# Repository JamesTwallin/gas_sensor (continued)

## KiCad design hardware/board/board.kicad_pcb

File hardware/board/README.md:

# Phone-companion board

A 66 × 36 mm, 4-layer board: bare ESP32-S3-MINI-1, two bare Figaro TGS sensors,
two ADS1115s, an SHT40, LiPo charging and a 5 V heater boost, plus a socket for
the [air blade](../air_blade/) (airflow thermistor and outside-air SHT40) and pads
for a CO module and a fan. The phone does the rest: position, display, storage
and the app. The electrical and Bluetooth spec is
[docs/phone_board.md](../../docs/phone_board.md). What the board measures and
why, with plots: [docs/board.md](../../docs/board.md).

Next to the first phone-companion board, with what is new boxed:

**Status: made and working.** JLCPCB made and assembled the boards, and they
passed a bench test on 2026-10-22. Three things to know when you first power one:

- **The boards arrive with blank flash.** Nothing runs until you flash the
  firmware.
- **The power switch (SW1) must be ON, even on USB.** It gates the 3.3 V
  regulator, so with it off the ESP32 has no power and the USB port does not
  appear.
- **The first flash needs the BOOT and RESET buttons.** Hold BOOT, press and
  release RESET, then let go of BOOT, and do a full upload (see
  [Firmware](#firmware)).

The board **fits the printed case** ([hardware/enclosure](../enclosure/),
`case.scad`): the mounting holes, sensor cans, USB-C, power switch, LED, BOOT
button and the SHT40 tongue are where the first board had them. The RST button
sits right above BOOT, so use the current front shell, `stl/front.stl`: it has
RST's pen hole in the right place and a slot for the air blade between the
sensor caps. The back shell is `stl/back.stl` and the car mount
`stl/car_adapter.stl`.

The board adds what the first survey analysis ([docs/REPORT.md](../../docs/REPORT.md))
showed was missing:

- **Airflow.** Air moving over the gas sensors cools their heaters and moves
  their readings as much as a small gas plume. The first board could not
  measure it.
- **Outside air.** The on-board SHT40 reads the air *inside the case*: on every
  drive it read 0.6–0.9 °C warmer at walking pace than at motorway speed, and
  28–32 °C during an indoor stop, because the heaters warm the case and airflow
  cools it. The detector needs the temperature and humidity of the air the
  sensors are sampling. The air blade carries a second SHT40 out in the air
  beside the sensor caps.
- **Exhaust versus gas.** Exhaust contains CO; mains gas does not.

## The air blade cannot be fitted yet

**Do not order the current air blade** ([hardware/air_blade](../air_blade/)).
J3, the board's socket for it, sits in a 3.8 mm gap between the two sensor cans,
which are 13 mm tall, and its pads stop 0.3 mm short of the blade's notch. There
is no realistic way to get a soldering iron in there and join the blade to the
pads. The blade is being redesigned. Until then the board runs without it: the
firmware uses the on-board SHT40 and reports no airflow.

## Layout

The ESP32 sits at the rear with its antenna over the left edge. The two Figaro
cans are at the front edge. USB-C is on the bottom edge and the switch on the
top edge, both in the middle.

- **Front (right) end: the gas inlet.** The two cans, each with a 0.5 Ω heater
  shunt beside its heater-return pin (R22 above CH4, R25 between the cans), and
  **J3**, the air blade's socket: five pads beside a notch in the board's end,
  in the gap between the cans where the air arrives (labelled BLADE). The
  [air blade](../air_blade/) is meant to stand in the notch, soldered to J3, and
  poke out through a slot in the case face. See above for why that does not
  work with the current blade.
- **Analogue block, just inboard of the cans.** ADS1115 #1 (U6) and #2 (U8)
  side by side; the heated thermistor's feed (R28/C24) above them;
  U8's 3V3-monitor divider (R33/R34/C27) below; the gas-sensor load networks.
- **Top edge.** **J4**, six pads for the CO module and a fan (labelled
  5V G TX RX 5V G), with R30 beside it.
- **Middle.** The boost loop (hand-routed) with the VSYS bulk capacitors C28/C29
  at its input; the battery and heater-rail dividers (R13/R14, R15/R16) in one
  row next to it.
- **Rear, by the ESP32.** The filter capacitors of the battery and heater-rail
  monitors (C13, C14) right at the ESP32 pins they feed.
- **Buttons and test pads.** RST and BOOT stacked one above the other by the
  USB edge; the serial/supply test pads in one row beside them, labelled
  TX RX GND 3V3.
- **SHT40 tongue (bottom-left).** The on-board SHT40, cut free on two sides by a
  slot. It reads the case air, and is logged as the case reading when the air
  blade is fitted.

## What it adds over the first board

| | Parts | What it does |
|---|---|---|
| **J3** + edge notch | 5 pads, 1.0 mm pitch: heated thermistor, GND, 3V3, SCL, SDA | socket for the [air blade](../air_blade/): an outside-air SHT40 (0x46, or 0x45) and the heated airflow thermistor, out in the air between the sensor caps. The current blade cannot be soldered to it (see above) |
| R28 1k, C24 | | feed the blade's heated thermistor 2.7 mW (about 1 °C above the air) |
| **U6** AIN2 | | reads the heated thermistor (16-bit); AIN3 is spare |
| GPIO1 / GPIO2 | C13, C14 at the pins | read VBAT and the heater rail on the ESP32's own ADC |
| **R22, R25** | 0.5 Ω, 0603 | in each sensor's heater return, so the heater current can be measured; fit 0 Ω links to switch this off |
| **U8** | ADS1115 at 0x49, C26 | reads both heater currents and, through R33/R34/C27, the 3.3 V rail (the thermistor dividers are not ratiometric to the ADC) |
| **J4** | 6 pads, 1.27 mm pitch: +5V, GND, TX in, RX out, +5V, GND; R30 1k | a Winsen ZE15-CO / ZE07-CO module (5–12 V, so it runs from the heater rail) and an optional 5 V fan. Pin 1 doubles as the +5 V test point |
| C28, C29 | 22 µF on VSYS | more margin when the heaters start on USB power alone (the first board browned out there) |
| SW2 (RST), TP1–TP4 | | RST right above BOOT; the test pads in a row beside them |

Pin by pin, where the board differs from the first board:

| | first board | this board |
|---|---|---|
| ADS1115 #1 (0x48) AIN2 / AIN3 | VBAT / 2, +5V_HTR / 2 | heated thermistor (air blade), spare |
| I²C bus | ADS1115 0x48, SHT40 0x44 | adds ADS1115 #2 0x49 and the air blade's SHT40 0x46 (or 0x45) |
| ADS1115 #2 (0x49) | — | AIN0 CH4 heater current, AIN1 LPG heater current, AIN2 +3V3 / 2, AIN3 spare |
| ESP32 GPIO1 / GPIO2 | backup reads of the gas taps (links never fitted) | VBAT / 2, +5V_HTR / 2 |
| GPIO43 / GPIO44 | test pads | test pads, and the CO module on J4 |
| Figaro pin 4 (heater −) | GND | 0.5 Ω shunt to GND |

## Firmware

```
pio run -d firmware/phone_board -e board --target upload
```

`board` is the default build target. On a new board, put the ESP32 into its
bootloader first (hold BOOT, tap RESET, release BOOT) and do a full upload,
because the flash is blank. After that, plain uploads work.

The firmware sends the board ID `rev-e` (a fixed value in the protocol). It
reads the heated thermistor on the ADS1115, and VBAT and the heater rail on the
ESP32. When the air blade's SHT40 answers (0x45 or 0x46), it supplies the
temperature and humidity (to the phone and to the detector) and the ambient for
the airflow calculation; the on-board readings are logged as `case_temp_c` /
`case_rh_pct` on USB serial, and the Info JSON says `"t_src":2`. Without the
blade it falls back to the on-board SHT40 (`"t_src":0`). The heater currents
(`ch4_htr_ma`, `lpg_htr_ma`) and the rail (`v3v3_mv`) go to the USB serial log
only for now: they are for a bench experiment first.

**The detector's coefficients were fitted on case-air readings.** With the
air blade fitted they need refitting from new surveys before the
detector's numbers mean anything ([docs/REPORT.md](../../docs/REPORT.md),
`python tools/replay.py fit`).

## The design is generated — edit `gen/design.py`, not the KiCad files

`gen/design.py` holds every part, net, LCSC number, placement, pre-routed track
and rule, and the scripts build the KiCad project from it:

| Step | Command | Output |
|---|---|---|
| custom symbols | `python gen/build_lib.py` | `lib/phone_board.kicad_sym` |
| schematic | `python gen/build_sch.py` | `board.kicad_sch` |
| board (placed, unrouted) | `"C:\Program Files\KiCad\9.0\bin\python.exe" gen/build_pcb.py` | `board.kicad_pcb`, `.kicad_pro` |
| autoroute | `...\python.exe gen/route.py` | routed board, GND pours + stitching vias |
| tidy silkscreen labels | `...\python.exe gen/tidy_silk.py` | |
| JLC placement | `...\python.exe gen/jlc_align.py` | `gen/jlc_placement.json` |
| fab files + renders | `python gen/export.py` | `production/`, `preview/` |
| relabel silkscreen only | `...\python.exe gen/build_pcb.py --silk-only` | edits the routed board in place |

Extra helpers: `gen/courtyards.py` prints footprint courtyards for checking
placement by hand; `gen/islands.py` and `gen/anchor_fills.py` find and anchor
unconnected ground-fill islands; `gen/add_keepouts.py` adds a keepout to a
routed board without re-routing; `gen/note_plots.py` draws the plots in
docs/board.md.

The middle of the board is dense, so a number of links are hand-routed
(`PREROUTE`) rather than left to the autorouter: the SDA trunk on In2, TXD0 to
the CO pads along the top strip on In2 and down B.Cu to the TX test pad, the
heater-rail divider feed, the two monitor lines from GPIO1/GPIO2 to their
capacitors, the 3V3-divider node, the J4 +5V pair, and short ground drops for
both ADS1115s, the air blade socket, the LPG shunt and the monitor capacitors
(where the ground fill cannot reach).

The air blade socket (J3) uses a project footprint,
`lib/phone_board.pretty/BladeSocket_1x05_P1.0mm`, and the notch is `NOTCHES` in
`gen/design.py`.

`route.py` needs the `JAVA` and `FREEROUTING` environment variables set to the
Java 25 runtime and the Freerouting 2.4.1 jar.

Checks: `kicad-cli pcb drc --schematic-parity board.kicad_pcb` and
`kicad-cli sch erc board.kicad_sch`.

Last run (2026-10-10, after adding the air blade socket and notch):
`kicad-cli pcb drc --schematic-parity` reports **0 violations, 0 unconnected
items, 0 schematic/board mismatches**; `kicad-cli sch erc` reports **0 errors,
0 warnings**; `gen/jlc_align.py` has corrected the CPL against LCSC's
footprints. Freerouting doesn't route the same way twice: after a rebuild, re-run
the checks.

## Ordering from JLCPCB

1. **PCB:** upload `production/gerbers.zip`. 4 layers, 1.6 mm. Minimums:
   0.2 mm track/clearance (0.15 mm at the SOT-563), 0.3 mm vias, and 0.2 mm drill
   for the via-in-pad GND vias under the ESP32, the charger and the two
   ADS1115s.
2. **Assembly:** top side, `production/bom.csv` and `production/cpl.csv` (already
   corrected for JLC's library by `gen/jlc_align.py`; still look over the preview,
   especially the pin-1 dots). Parts that are easy to miss in the BOM: the 0.5 Ω
   0603 shunts (FRL0603FR500TS, C2934253) and the second ADS1115 (C37593).
   **Do not order the current [air blade](../air_blade/)** with it: it cannot
   be soldered to J3 (see [above](#the-air-blade-cannot-be-fitted-yet)).
3. **Solder yourself:**
   - **Figaro TGS2611-E00 (S1, CH4) and TGS2610-D00 (S2, LPG)**, from RS
     Components (134-6647 and 134-6641). Burn them in for 4–7 days.
   - If used, **the CO module and fan on J4**
     ([docs/HARDWARE.md](../../docs/HARDWARE.md) section 2). The pads are 1.27 mm
     apart: solder thin wire straight on.

## Before you power it

Check the battery polarity (J2 pin 1 = −, pin 2 = +), and on first bring-up check
+3V3 on TP4 before fitting the sensors (SW1 must be ON). +5V_HTR is on J4 pin 1;
it stays at 0 V until the firmware drives GPIO7 high.

- **When an air blade is fitted, its tip must stand in free air,** 4.5 mm out of
  the slot, touching nothing: the heated thermistor reads airflow by how fast it
  loses heat.

## Known limitations

- The battery charger draws a little from the cell even when the board is off,
  the charge current is fixed at 500 mA, and the schematic is joined up by net
  labels rather than drawn wires.
- **The air blade cannot be fitted yet** (see above), so the airflow and
  outside-air readings are untested on this board.
- Still to be measured:
  - whether the heater current changes measurably with airflow (Figaro does not
    publish the heater's temperature coefficient);
  - the VBAT reading through the 1M/1M divider on the ESP32's ADC (C13 holds the
    charge; calibrate against a meter);
  - how much the blade's thermistor self-heats and how strongly it follows
    airflow (the still-air calibration and the airflow survey measure it);
  - whether a CO module and a fan both fit in the printed case.
- The air blade is soldered in and the CO module is wired, not connectorised: fine for
  a prototype, fragile for a fleet.

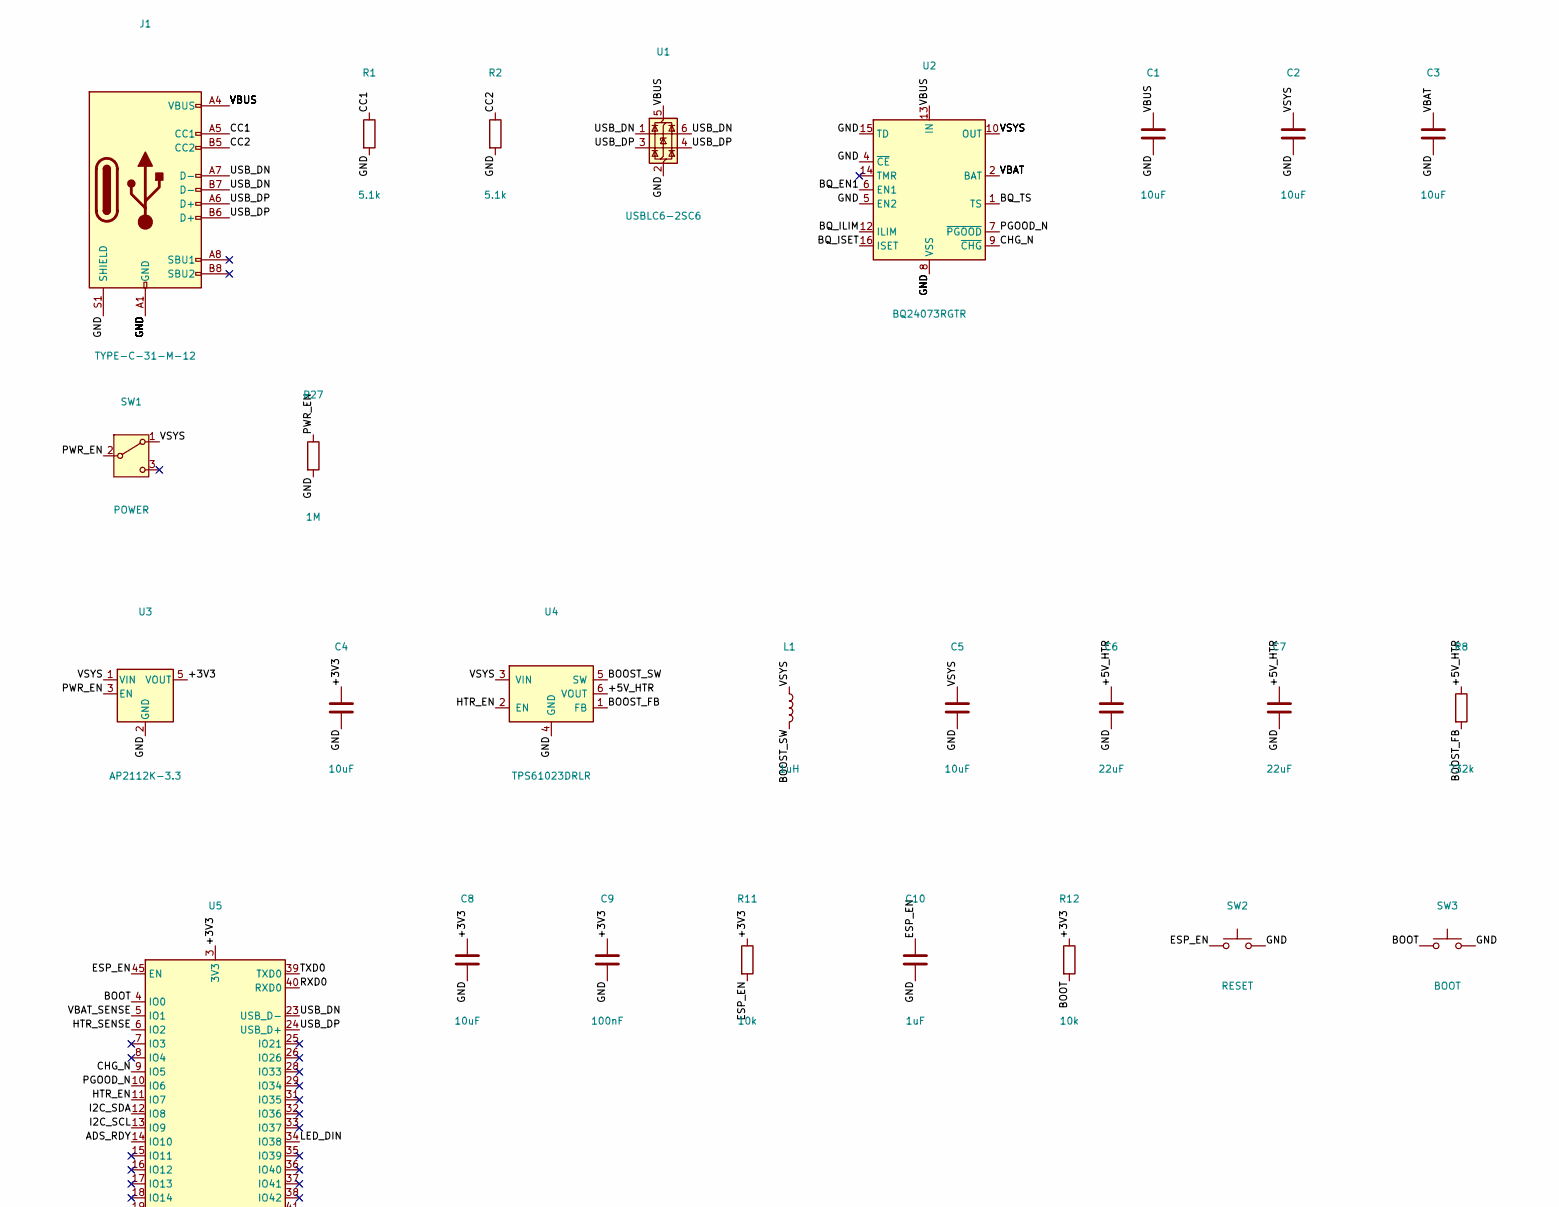
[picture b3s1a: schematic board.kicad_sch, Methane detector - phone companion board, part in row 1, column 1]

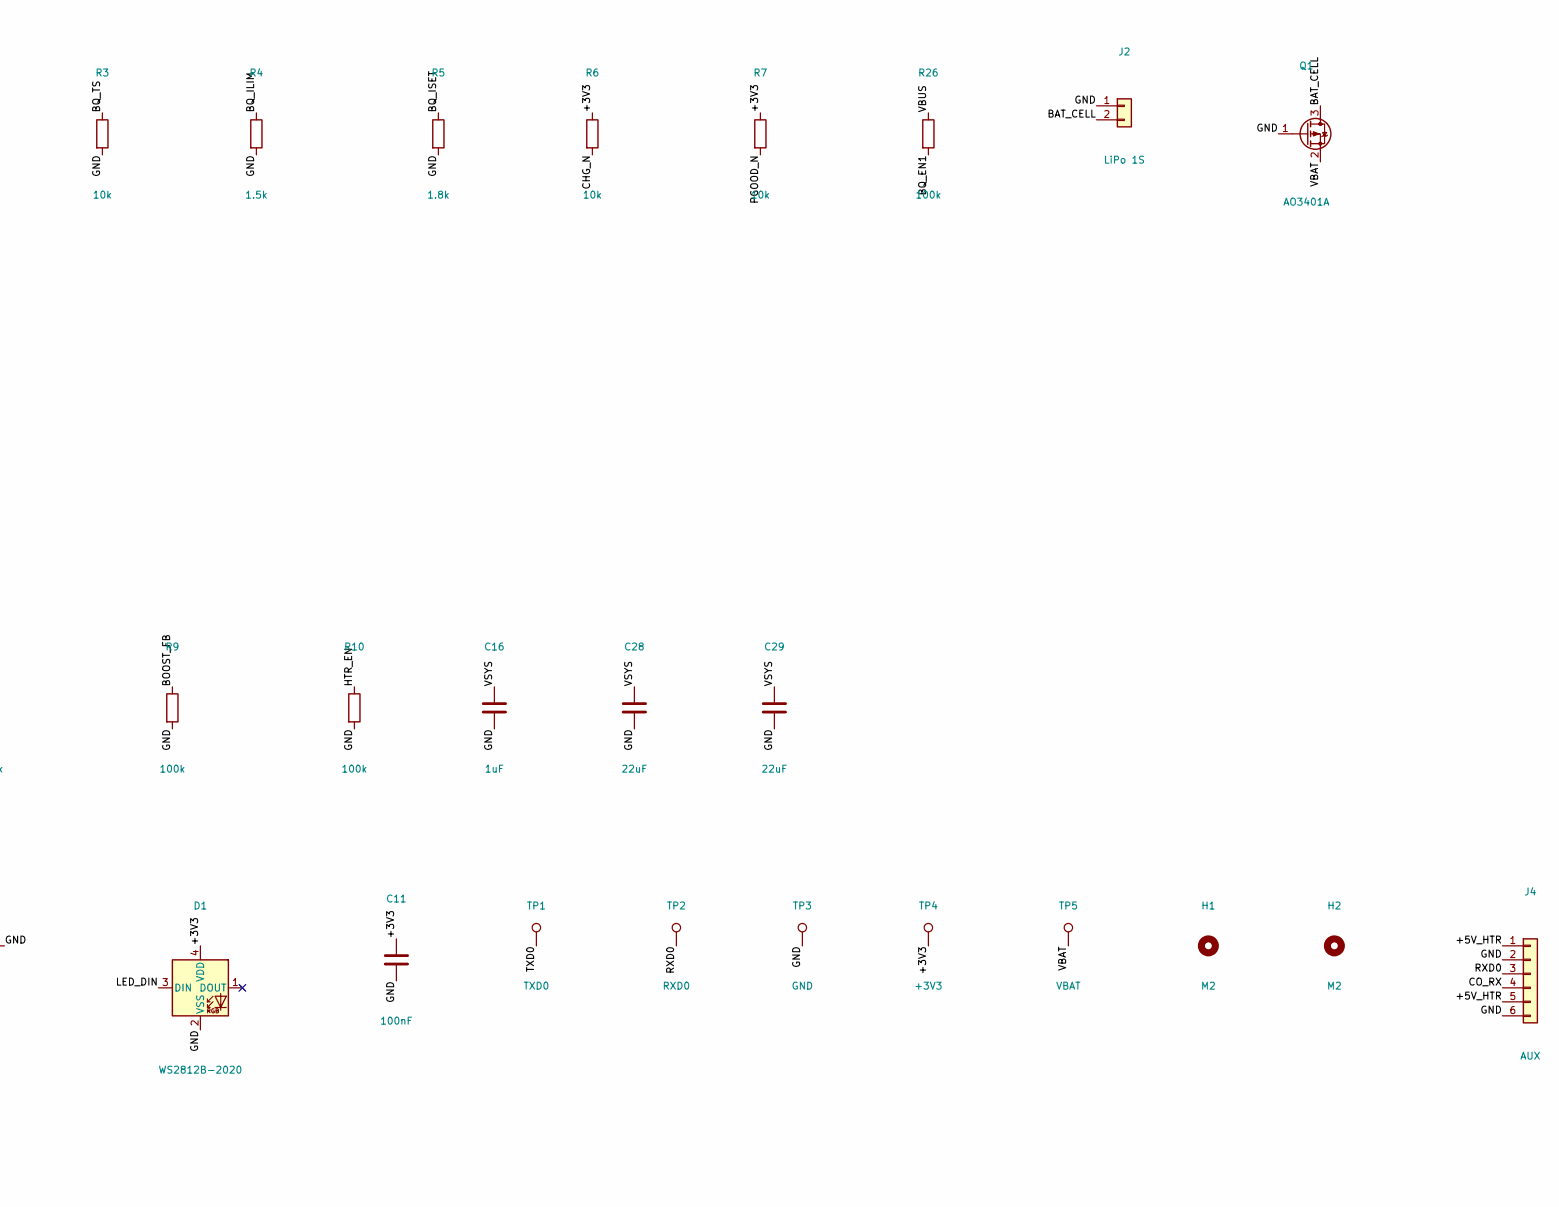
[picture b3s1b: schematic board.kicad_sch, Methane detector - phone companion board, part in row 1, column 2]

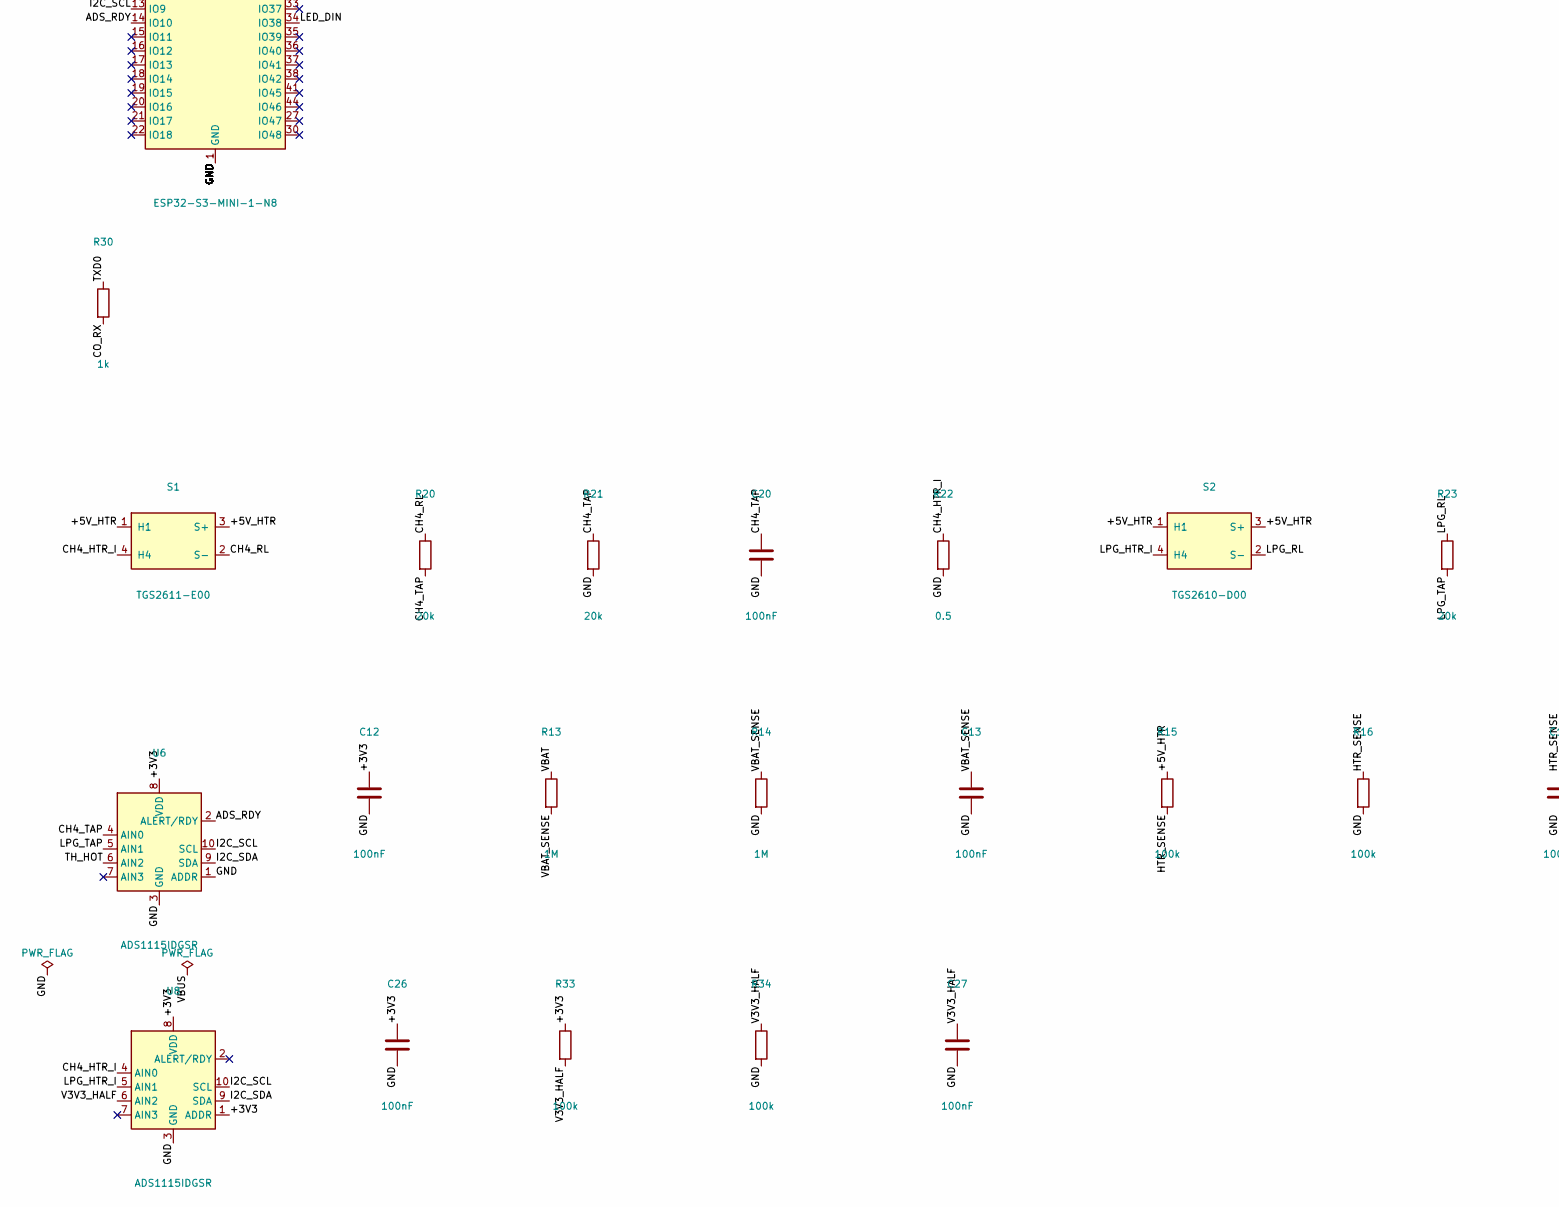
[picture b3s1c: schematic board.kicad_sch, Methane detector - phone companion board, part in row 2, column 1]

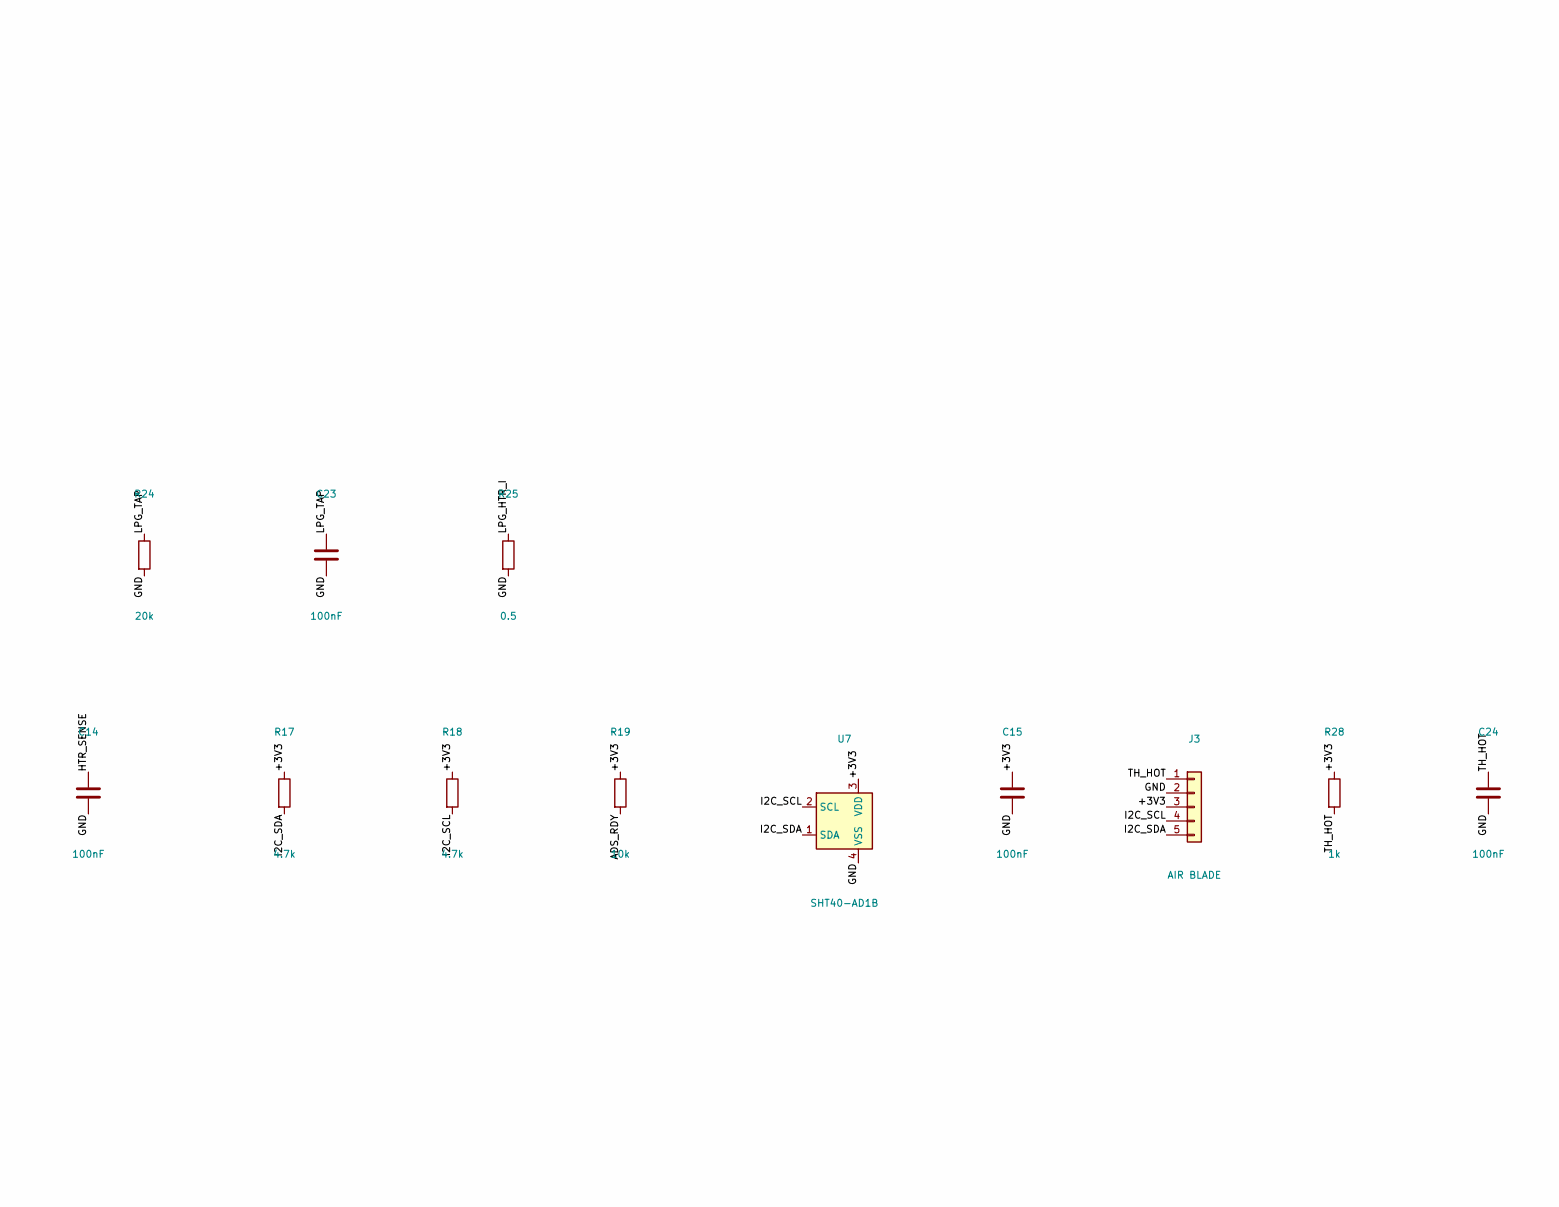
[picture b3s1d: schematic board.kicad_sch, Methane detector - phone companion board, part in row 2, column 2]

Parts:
C1: 10uF; C_0805_2012Metric; LCSC C15850
C2, C3, C4, C5, C8: 10uF; C_0603_1608Metric; LCSC C19702
C6, C7, C28, C29: 22uF; C_0805_2012Metric; LCSC C45783
C9, C11, C12, C13, C14, C15, C20, C23, C24, C26, C27: 100nF; C_0402_1005Metric; LCSC C1525
C10, C16: 1uF; C_0402_1005Metric; LCSC C52923
D1: WS2812B-2020; LED_WS2812B-2020_PLCC4_2.0x2.0mm; LCSC C52917434
H1, H2: M2; MountingHole_2.2mm_M2
J1: TYPE-C-31-M-12; USB_C_Receptacle_HRO_TYPE-C-31-M-12; LCSC C165948
J2: LiPo 1S; JST_PH_S2B-PH-SM4-TB_1x02-1MP_P2.00mm_Horizontal; LCSC C295747
J3: AIR BLADE; BladeSocket_1x05_P1.0mm
J4: AUX; PinHeader_1x06_P1.27mm_Vertical
L1: 1uH; L_Sunlord_SWPA4030S; MPN SWPA4030S1R0NT; LCSC C42193
Q1: AO3401A; SOT-23; LCSC C15127
R1, R2: 5.1k; R_0402_1005Metric; LCSC C25905
R3, R6, R7, R11, R12, R19: 10k; R_0402_1005Metric; LCSC C25744
R4: 1.5k; R_0402_1005Metric; LCSC C25867
R5: 1.8k; R_0402_1005Metric; LCSC C25871
R8: 732k; R_0402_1005Metric; LCSC C27016
R9, R10, R15, R16, R26, R33, R34: 100k; R_0402_1005Metric; LCSC C25741
R13, R14, R27: 1M; R_0402_1005Metric; LCSC C26083
R17, R18: 4.7k; R_0402_1005Metric; LCSC C25900
R20, R21, R23, R24: 20k; R_0402_1005Metric; LCSC C25765
R22, R25: 0.5; R_0603_1608Metric; LCSC C2934253
R28, R30: 1k; R_0402_1005Metric; LCSC C11702
S1: TGS2611-E00; TO-5-4; MPN TGS2611-E00
S2: TGS2610-D00; TO-5-4; MPN TGS2610-D00
SW1: POWER; SW_SPDT_Shouhan_MSK12C02; LCSC C431540
SW2: RESET; SW_Push_1P1T_XKB_TS-1187A; LCSC C318884
SW3: BOOT; SW_Push_1P1T_XKB_TS-1187A; LCSC C318884
TP1: TXD0; TestPoint_Pad_D1.0mm
TP2: RXD0; TestPoint_Pad_D1.0mm
TP3: GND; TestPoint_Pad_D1.0mm
TP4: +3V3; TestPoint_Pad_D1.0mm
TP5: VBAT; TestPoint_Pad_D1.0mm
U1: USBLC6-2SC6; SOT-23-6; LCSC C7519
U2: BQ24073RGTR; VQFN-16-1EP_3x3mm_P0.5mm_EP1.6x1.6mm; LCSC C15220
U3: AP2112K-3.3; SOT-23-5; LCSC C51118
U4: TPS61023DRLR; SOT-563; LCSC C919459
U5: ESP32-S3-MINI-1-N8; ESP32-S2-MINI-1; LCSC C2913206
U6, U8: ADS1115IDGSR; MSOP-10_3x3mm_P0.5mm; LCSC C37593
U7: SHT40-AD1B; Sensirion_DFN-4_1.5x1.5mm_P0.8mm_SHT4x_NoCentralPad; MPN SHT40-AD1B-R2; LCSC C2909890

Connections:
/+3V3: C4.1, C8.1, C9.1, C11.1, C12.1, C15.1, C26.1, D1.4 (VDD), J3.3, R6.1, R7.1, R11.1, R12.1, R17.1, R18.1, R19.1, R28.1, R33.1, TP4.1, U3.5 (VOUT), U5.3 (3V3), U6.8 (VDD), U7.3 (VDD), U8.1 (ADDR), U8.8 (VDD)
/+5V_HTR: C6.1, C7.1, J4.1, J4.5, R8.1, R15.1, S1.1 (H1), S1.3 (S+), S2.1 (H1), S2.3 (S+), U4.6 (VOUT)
/ADS_RDY: R19.2, U5.14 (IO10), U6.2 (ALERT/RDY)
/BAT_CELL: J2.2, Q1.3 (D)
/BOOST_FB: R8.2, R9.1, U4.1 (FB)
/BOOST_SW: L1.2, U4.5 (SW)
/BOOT: R12.2, SW3.1, U5.4 (IO0)
/BQ_EN1: R26.2, U2.6 (EN1)
/BQ_ILIM: R4.1, U2.12 (ILIM)
/BQ_ISET: R5.1, U2.16 (ISET)
/BQ_TS: R3.1, U2.1 (TS)
/CC1: J1.A5 (CC1), R1.1
/CC2: J1.B5 (CC2), R2.1
/CH4_HTR_I: R22.1, S1.4 (H4), U8.4 (AIN0)
/CH4_RL: R20.1, S1.2 (S-)
/CH4_TAP: C20.1, R20.2, R21.1, U6.4 (AIN0)
/CHG_N: R6.2, U2.9 (~CHG), U5.9 (IO5)
/CO_RX: J4.4, R30.2
/ESP_EN: C10.1, R11.2, SW2.1, U5.45 (EN)
/GND: C1.2, C2.2, C3.2, C4.2, C5.2, C6.2, C7.2, C8.2, C9.2, C10.2, C11.2, C12.2, C13.2, C14.2, C15.2, C16.2, C20.2, C23.2, C24.2, C26.2, C27.2, C28.2, C29.2, D1.2 (VSS), J1.A1 (GND), J1.A12 (GND), J1.B1 (GND), J1.B12 (GND), J1.S1 (SHIELD), J2.1, J3.2, J4.2, J4.6, Q1.1 (G), R1.2, R2.2, R3.2, R4.2, R5.2, R9.2, R10.2, R14.2, R16.2, R21.2, R22.2, R24.2, R25.2, R27.2, R34.2, SW2.2, SW3.2, TP3.1, U1.2 (GND), U2.4 (~CE), U2.5 (EN2), U2.8 (VSS), U2.15 (TD), U2.17 (VSS), U3.2 (GND), U4.4 (GND), U5.1 (GND), U5.2 (GND), U5.42 (GND), U5.43 (GND), U5.46 (GND), U5.47 (GND), U5.48 (GND), U5.49 (GND), U5.50 (GND), U5.51 (GND), U5.52 (GND), U5.53 (GND), U5.54 (GND), U5.55 (GND), U5.56 (GND), U5.57 (GND), U5.58 (GND), U5.59 (GND), U5.60 (GND), U5.61 (GND), U5.62 (GND), U5.63 (GND), U5.64 (GND), U5.65 (GND), U6.1 (ADDR), U6.3 (GND), U7.4 (VSS), U8.3 (GND)
/HTR_EN: R10.1, U4.2 (EN), U5.11 (IO7)
/HTR_SENSE: C14.1, R15.2, R16.1, U5.6 (IO2)
/I2C_SCL: J3.4, R18.2, U5.13 (IO9), U6.10 (SCL), U7.2 (SCL), U8.10 (SCL)
/I2C_SDA: J3.5, R17.2, U5.12 (IO8), U6.9 (SDA), U7.1 (SDA), U8.9 (SDA)
/LED_DIN: D1.3 (DIN), U5.34 (IO38)
/LPG_HTR_I: R25.1, S2.4 (H4), U8.5 (AIN1)
/LPG_RL: R23.1, S2.2 (S-)
/LPG_TAP: C23.1, R23.2, R24.1, U6.5 (AIN1)
/PGOOD_N: R7.2, U2.7 (~PGOOD), U5.10 (IO6)
/PWR_EN: R27.1, SW1.2 (B), U3.3 (EN)
/RXD0: J4.3, TP2.1, U5.40 (RXD0)
/TH_HOT: C24.1, J3.1, R28.2, U6.6 (AIN2)
/TXD0: R30.1, TP1.1, U5.39 (TXD0)
/USB_DN: J1.A7 (D-), J1.B7 (D-), U1.1 (I/O1), U1.6 (I/O1), U5.23 (USB_D-)
/USB_DP: J1.A6 (D+), J1.B6 (D+), U1.3 (I/O2), U1.4 (I/O2), U5.24 (USB_D+)
/V3V3_HALF: C27.1, R33.2, R34.1, U8.6 (AIN2)
/VBAT: C3.1, Q1.2 (S), R13.1, TP5.1, U2.2 (BAT), U2.3 (BAT)
/VBAT_SENSE: C13.1, R13.2, R14.1, U5.5 (IO1)
/VBUS: C1.1, J1.A4 (VBUS), J1.A9 (VBUS), J1.B4 (VBUS), J1.B9 (VBUS), R26.1, U1.5 (VBUS), U2.13 (IN)
/VSYS: C2.1, C5.1, C16.1, C28.1, C29.1, L1.1, SW1.1 (A), U2.10 (OUT), U2.11 (OUT), U3.1 (VIN), U4.3 (VIN)

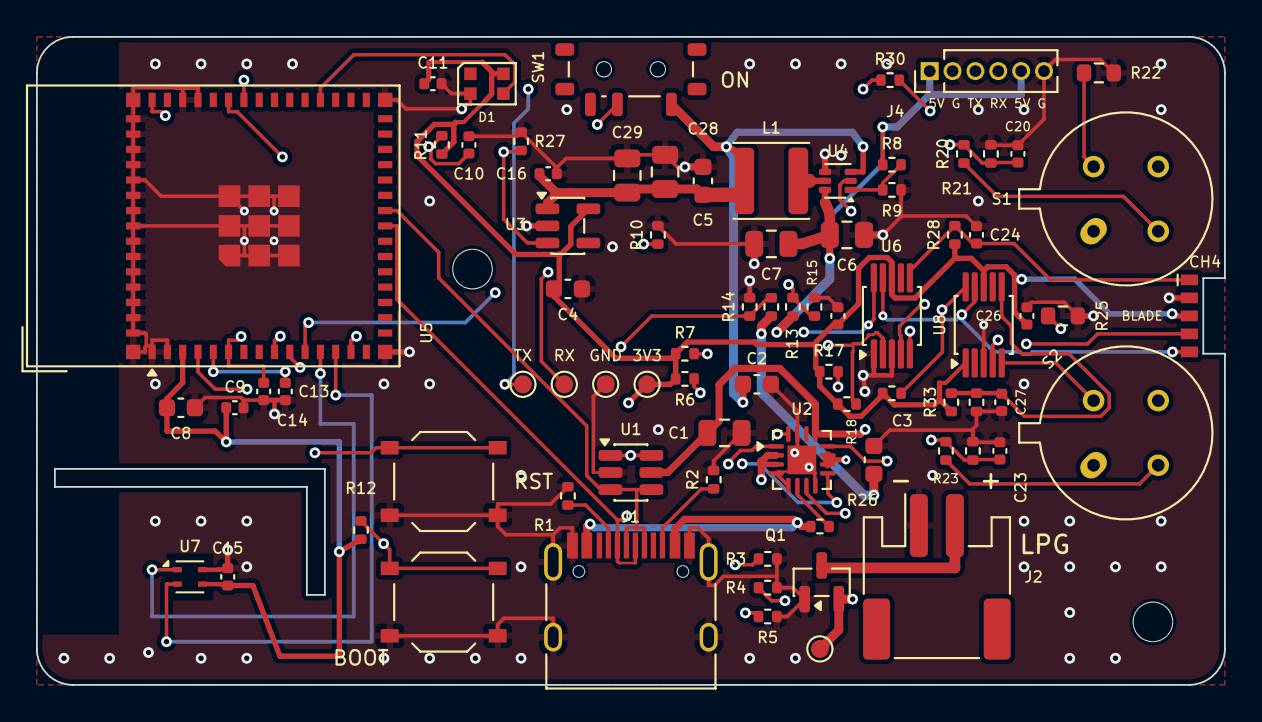
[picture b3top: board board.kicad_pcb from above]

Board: 4 copper layers, 66.0 x 36.0 mm, 81 parts (0 on the bottom side), 40 nets.

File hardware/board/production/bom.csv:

Comment,Designator,Footprint,LCSC Part #
10uF,C1,C_0805_2012Metric,C15850
1uF,"C10,C16",C_0402_1005Metric,C52923
10uF,"C2,C3,C4,C5,C8",C_0603_1608Metric,C19702
22uF,"C28,C29,C6,C7",C_0805_2012Metric,C45783
100nF,"C11,C12,C13,C14,C15,C20,C23,C24,C26,C27,C9",C_0402_1005Metric,C1525
WS2812B-2020,D1,LED_WS2812B-2020_PLCC4_2.0x2.0mm,C52917434
TYPE-C-31-M-12,J1,USB_C_Receptacle_HRO_TYPE-C-31-M-12,C165948
LiPo 1S,J2,JST_PH_S2B-PH-SM4-TB_1x02-1MP_P2.00mm_Horizontal,C295747
1uH,L1,L_Sunlord_SWPA4030S,C42193
AO3401A,Q1,SOT-23,C15127
5.1k,"R1,R2",R_0402_1005Metric,C25905
4.7k,"R17,R18",R_0402_1005Metric,C25900
20k,"R20,R21,R23,R24",R_0402_1005Metric,C25765
0.5,"R22,R25",R_0603_1608Metric,C2934253
100k,"R10,R15,R16,R26,R33,R34,R9",R_0402_1005Metric,C25741
1M,"R13,R14,R27",R_0402_1005Metric,C26083
1k,"R28,R30",R_0402_1005Metric,C11702
10k,"R11,R12,R19,R3,R6,R7",R_0402_1005Metric,C25744
1.5k,R4,R_0402_1005Metric,C25867
1.8k,R5,R_0402_1005Metric,C25871
732k,R8,R_0402_1005Metric,C27016
POWER,SW1,SW_SPDT_Shouhan_MSK12C02,C431540
RESET,SW2,SW_Push_1P1T_XKB_TS-1187A,C318884
BOOT,SW3,SW_Push_1P1T_XKB_TS-1187A,C318884
USBLC6-2SC6,U1,SOT-23-6,C7519
BQ24073RGTR,U2,VQFN-16-1EP_3x3mm_P0.5mm_EP1.6x1.6mm,C15220
AP2112K-3.3,U3,SOT-23-5,C51118
TPS61023DRLR,U4,SOT-563,C919459
ESP32-S3-MINI-1-N8,U5,ESP32-S2-MINI-1,C2913206
ADS1115IDGSR,"U6,U8",MSOP-10_3x3mm_P0.5mm,C37593
SHT40-AD1B,U7,Sensirion_DFN-4_1.5x1.5mm_P0.8mm_SHT4x_NoCentralPad,C2909890

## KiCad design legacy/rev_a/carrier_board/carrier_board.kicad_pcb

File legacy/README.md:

# Legacy

Earlier versions, kept for reference. **Nothing here is the current design**:
that is the rev C board in [hardware/phone_board](../hardware/phone_board/) with
the firmware in [firmware/phone_board](../firmware/phone_board/) and the phone
app in [app](../app/). Start from the [top-level README](../README.md).

| Folder | What | Why it is here |
|---|---|---|
| [rev_a](rev_a/) | The first prototype: a Waveshare ESP32-S3-Zero and sensor modules on a carrier board, with its own OLED, GNSS receiver and microSD card. Firmware, KiCad project, connection spec and photos. | Replaced by the phone-companion boards (rev B onwards), which move the display, position and storage onto a phone. |
| [enclosure](enclosure/) | The two box-and-lid case models. | Replaced by the front-shell-and-battery-tray case in [hardware/enclosure](../hardware/enclosure/). |

The rev B board (the 66 × 36 mm layout that was built and tested) is not a
folder: rev C replaced it in place. Its files are at the git tag `rev-b`.

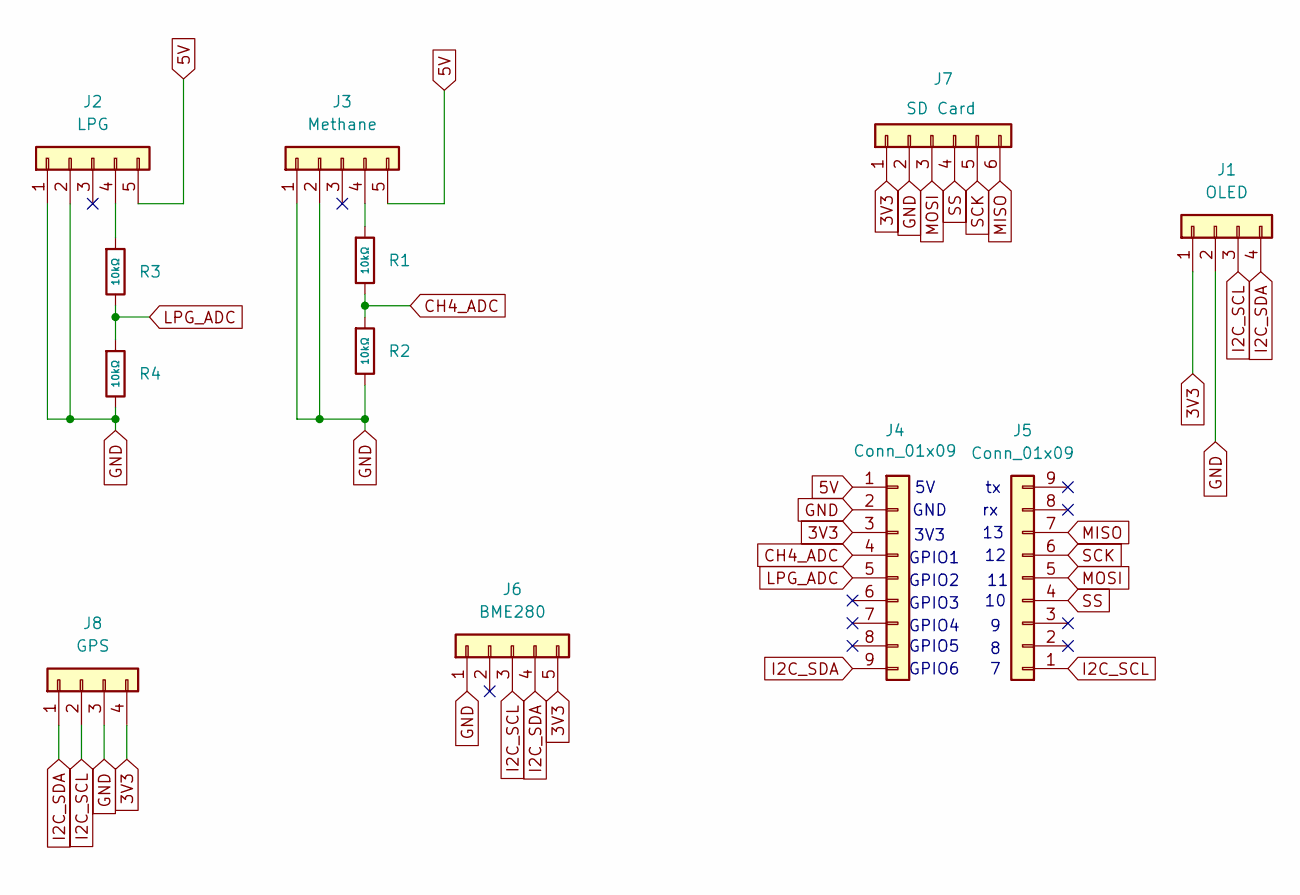
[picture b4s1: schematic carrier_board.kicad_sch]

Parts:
J1: OLED; PinSocket_1x04_P2.54mm_Vertical
J2: LPG; PinSocket_1x05_P2.54mm_Vertical
J3: Methane; PinSocket_1x05_P2.54mm_Vertical
J4, J5: Conn_01x09; PinSocket_1x09_P2.54mm_Vertical
J6: BME280; PinSocket_1x06_P2.54mm_Vertical
J7: SD Card; PinSocket_1x06_P2.54mm_Vertical
J8: GPS; PinHeader_1x04_P2.54mm_Horizontal
R1, R2, R3, R4: 10kΩ; R_0603; Overload Voltage (Max) 75V; Tolerance ±1%; Part 0603WAF1002T5E; LCSC C25804

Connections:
3V3: J1.1, J4.3, J6.5, J7.1, J8.4
5V: J2.5, J3.5, J4.1
CH4_ADC: J4.4, R1.2, R2.1
GND: J1.2, J2.1, J2.2, J3.1, J3.2, J4.2, J6.1, J7.2, J8.3, R2.2, R4.2
I2C_SCL: J1.3, J5.1, J6.3, J8.2
I2C_SDA: J1.4, J4.9, J6.4, J8.1
LPG_ADC: J4.5, R3.2, R4.1
MISO: J5.7, J7.6
MOSI: J5.5, J7.3
unnamed: J2.4, R3.1
unnamed: J3.4, R1.1
SCK: J5.6, J7.5
SS: J5.4, J7.4

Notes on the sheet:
GPIO1
GND
GPIO2
GPIO3
3V3
GPIO4
GPIO6
GPIO5

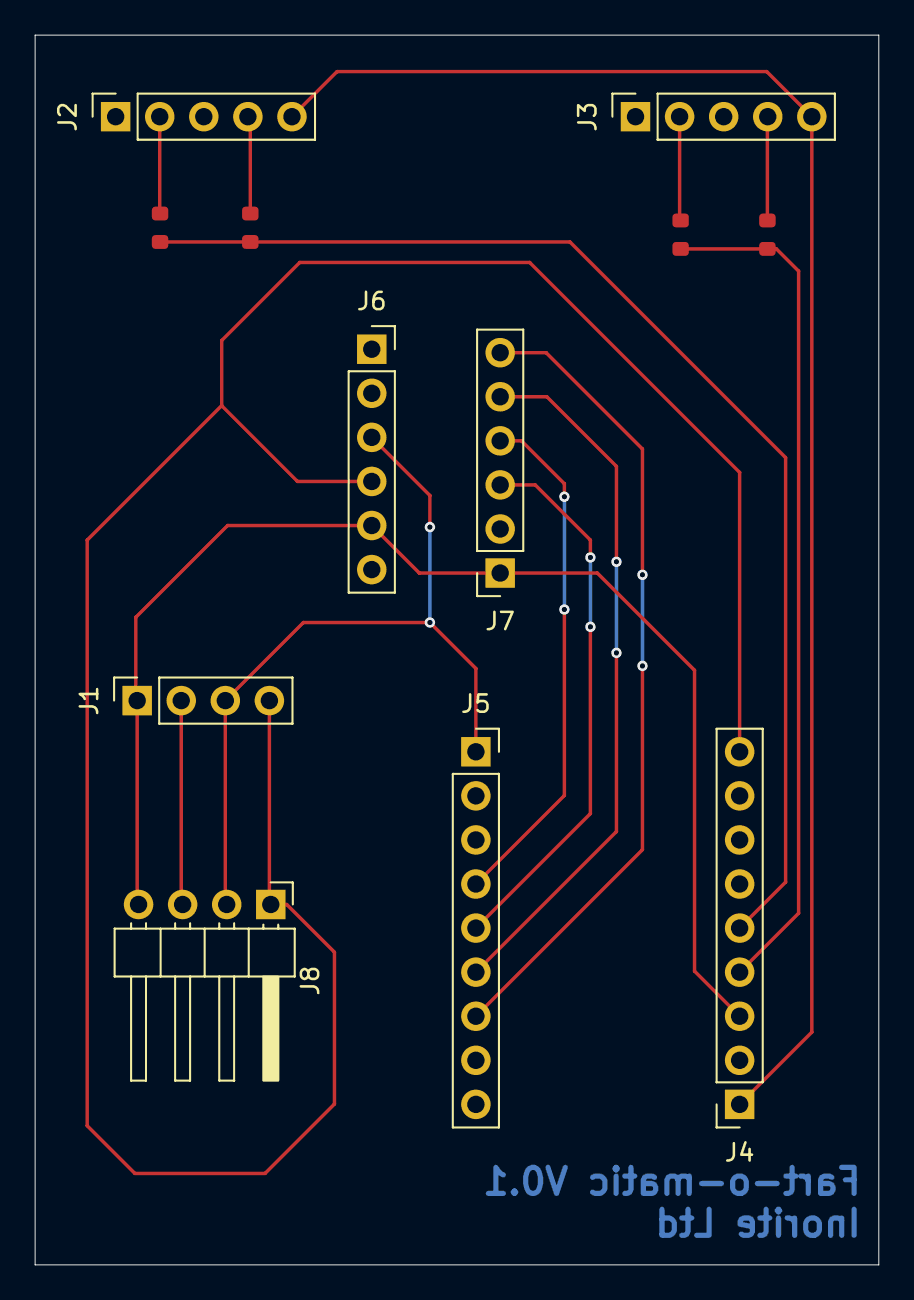
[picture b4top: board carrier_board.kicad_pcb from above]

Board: 2 copper layers, 48.6 x 70.9 mm, 12 parts (0 on the bottom side), 13 nets.

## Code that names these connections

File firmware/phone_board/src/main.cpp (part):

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// are on the ESP32's own ADC (GPIO1/GPIO2, oversampled, calibrated
// analogReadMilliVolts), so they and the heater check (bit4) keep working.
//
// Heaters: HTR_EN (GPIO7) is the boost converter's enable and has a 100k
// pull-down on the board, so the heaters stay off until setup() drives it HIGH.
// Low-battery heater cutoff: the ~115 mA heaters are most of the load, so when
// VBAT stays below 3.3 V for 10 s the firmware drives HTR_EN low and sets flag
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
// ---- Pins (docs/phone_board.md, ESP32-S3-MINI-1-N8 pin map) -----------------
static const uint8_t PIN_BOOT_BUTTON = 0;   // active low, tact switch to GND
static const uint8_t PIN_CHG_N = 5;         // BQ24073 CHG, low = charging
static const uint8_t PIN_PGOOD_N = 6;       // BQ24073 PGOOD, low = USB power good
static const uint8_t PIN_HTR_EN = 7;        // 100k pull-down: drive HIGH = heaters on, LOW = off
static const uint8_t PIN_I2C_SDA = 8;
static const uint8_t PIN_I2C_SCL = 9;
static const uint8_t PIN_ADS_RDY = 10;      // ADS1115 ALERT/RDY, active low
static const uint8_t PIN_LED_DIN = 38;      // WS2812-class status LED
static const uint8_t PIN_VBAT_ADC = 1;      // VBAT / 2 (1M/1M + 100 nF)
static const uint8_t PIN_HTR_ADC = 2;       // +5V_HTR / 2 (100k/100k + 100 nF)
static const uint8_t PIN_CO_RX = 44;        // HW_CO: RXD0 test pad TP2 <- module TX
static const uint8_t PIN_CO_TX = 43;        // TXD0 test pad TP1 (left unconnected)
static const uint8_t PIN_MEMS_HTR_EN = 12;  // MEMS rig: MEMS heater P-FET, HIGH = on, 100k pull-down

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
  bool ready;
  if (adsState.useRdyPin) {
    ready = (digitalRead(PIN_ADS_RDY) == LOW);
  } else {
    ready = (elapsedUs >= ADS_POLL_AT_US) && ads.conversionComplete();
  }
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  ledShown = c;
  // Standard WS2812B/SK6812: the core puts GRB on the wire from (r, g, b).
#if ESP_ARDUINO_VERSION_MAJOR >= 3
  rgbLedWrite(PIN_LED_DIN, r, g, b);
#else
  neopixelWrite(PIN_LED_DIN, r, g, b);
#endif
}

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}
#endif

// Low-battery heater cutoff. HTR_EN (GPIO7) is the boost enable with a 100k
// pull-down on the board: HIGH = heaters on, LOW = heaters off. Heaters go
// off once VBAT has stayed below HEATER_CUTOFF_MV for HEATER_CUTOFF_HOLD_MS and
// come back only above HEATER_RESTORE_MV. An unknown VBAT (0, no ADS1115)
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
#if HW_MEMS
// MEMS blade heaters (PIN_MEMS_HTR_EN, 100k pull-down: off until driven HIGH).
// They run from +5V_HTR, so they only get power while HTR_EN is high anyway; the pin
// still goes low whenever HTR_EN does. On again MEMS_STAGGER_MS after HTR_EN comes back
// (heaterOnSinceMs), so the boost never starts into all four heaters at once.
static bool memsBlade = false;            // blade fitted (tap test)
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#endif

static void driveHeaterPin() {
  digitalWrite(PIN_HTR_EN, (heatersEnabled && !heatersOffLowBatt) ? HIGH : LOW);
#if HW_MEMS
  if (!(heatersEnabled && !heatersOffLowBatt)) setMemsHeater(false, 0);
#endif
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  vbatMv = clampU16(readFallbackMv(PIN_VBAT_ADC) * VBAT_RATIO);
  bool heaterKnown = true;
  float heaterRailMv = readFallbackMv(PIN_HTR_ADC) * HEATER_RATIO;
  updateHeaterCutoff(nowMs, vbatMv, digitalRead(PIN_PGOOD_N) == LOW);
  if (heatersOffLowBatt) flags |= FLAG_HEATERS_OFF;
  if (heaterKnown) {
    heaterMv = clampU16(heaterRailMv);
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  if (tOk && hOk) flags |= FLAG_BME_OK;

  // Charger status (open-drain with external pull-ups: low = asserted).
  if (digitalRead(PIN_PGOOD_N) == LOW) flags |= FLAG_USB_POWER;
  if (digitalRead(PIN_CHG_N) == LOW) flags |= FLAG_CHARGING;

  if (markPending) {
    flags |= FLAG_BUTTON;
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  // pull-down held the boost off through the bootloader; latch HIGH before
  // enabling the driver so there is no LOW glitch.
  setCpuFrequencyMhz(CPU_MHZ);
  digitalWrite(PIN_HTR_EN, HIGH);
  pinMode(PIN_HTR_EN, OUTPUT);
  heatersEnabled = true;
  rtcHeaterOnMs = millis();
  heaterOnSinceMs = rtcHeaterOnMs;
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  while (!Serial && millis() - waitStart < 1500) delay(10);

  pinMode(PIN_BOOT_BUTTON, INPUT_PULLUP);
  pinMode(PIN_CHG_N, INPUT);  // external 10k pull-ups
  pinMode(PIN_PGOOD_N, INPUT);
  pinMode(PIN_ADS_RDY, INPUT);
#if HW_MEMS
  // MEMS heaters stay off (the pull-down already holds them) until the blade check and
  // the stagger say otherwise.
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  memsBurnH = memsBurnS / 3600;
#endif
#if HW_CO
  Serial1.begin(CO_BAUD, SERIAL_8N1, PIN_CO_RX, PIN_CO_TX);
#endif

  Wire.begin(PIN_I2C_SDA, PIN_I2C_SCL);
  Wire.setClock(I2C_CLOCK_HZ);

  Serial.println();
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
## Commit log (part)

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2026-06-24 Atmospheric methane detector — initial public release
    ESP32-S3 firmware for a GPS-tagged handheld methane survey instrument, the
    KiCad carrier-board design, and the Python analysis tools (survey videos + maps).
